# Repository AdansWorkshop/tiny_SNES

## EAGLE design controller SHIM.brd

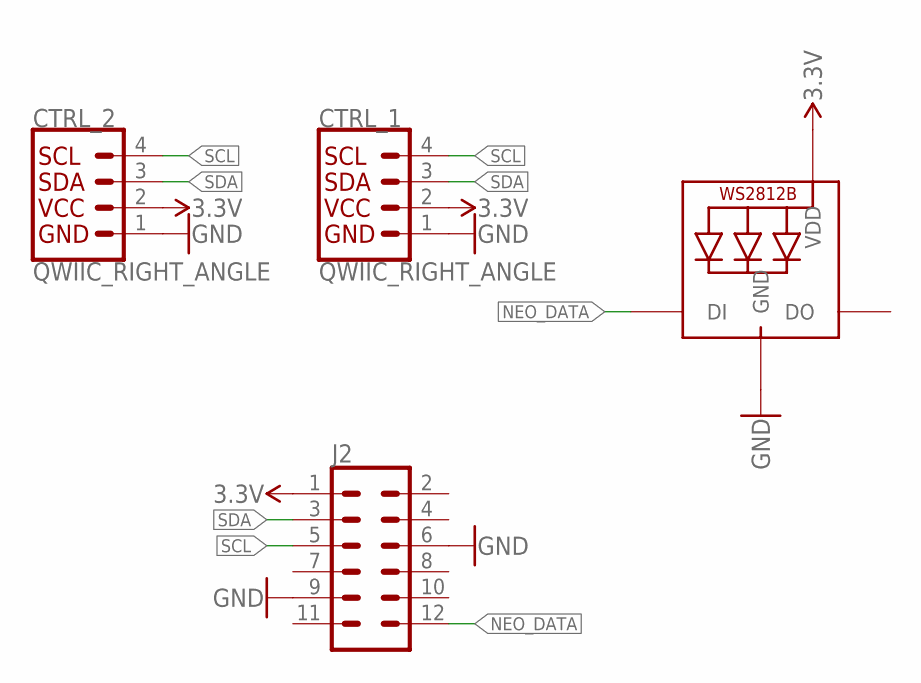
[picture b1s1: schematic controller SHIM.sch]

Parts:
CTRL_1, CTRL_2: QWIIC_RIGHT_ANGLE; JST04_1MM_RA
J2: CONN_06X2SMD_FEMALE; 2X6_SMD
STATUS_LED: WS2812B3535; LED3535

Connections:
3.3V: CTRL_1.2, CTRL_2.2, J2.1, STATUS_LED.2 (VDD)
GND: CTRL_1.1, CTRL_2.1, J2.6, J2.9, STATUS_LED.4 (GND)
NEO_DATA: J2.12, STATUS_LED.1 (DI)
SCL: CTRL_1.4, CTRL_2.4, J2.5
SDA: CTRL_1.3, CTRL_2.3, J2.3

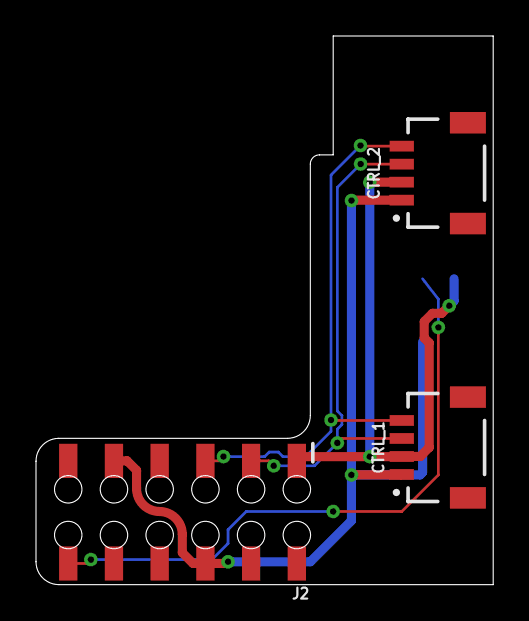
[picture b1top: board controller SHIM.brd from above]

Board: 2 copper layers, 25.4 x 30.5 mm, 4 parts (1 on the bottom side), 5 nets.

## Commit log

2023-10-21 add controller port board files

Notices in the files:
parts and their libraries:
SparkFun-Connectors: Licensing: Creative Commons ShareAlike 4.0 International - https://creativecommons.org/licenses/by-sa/4.0
